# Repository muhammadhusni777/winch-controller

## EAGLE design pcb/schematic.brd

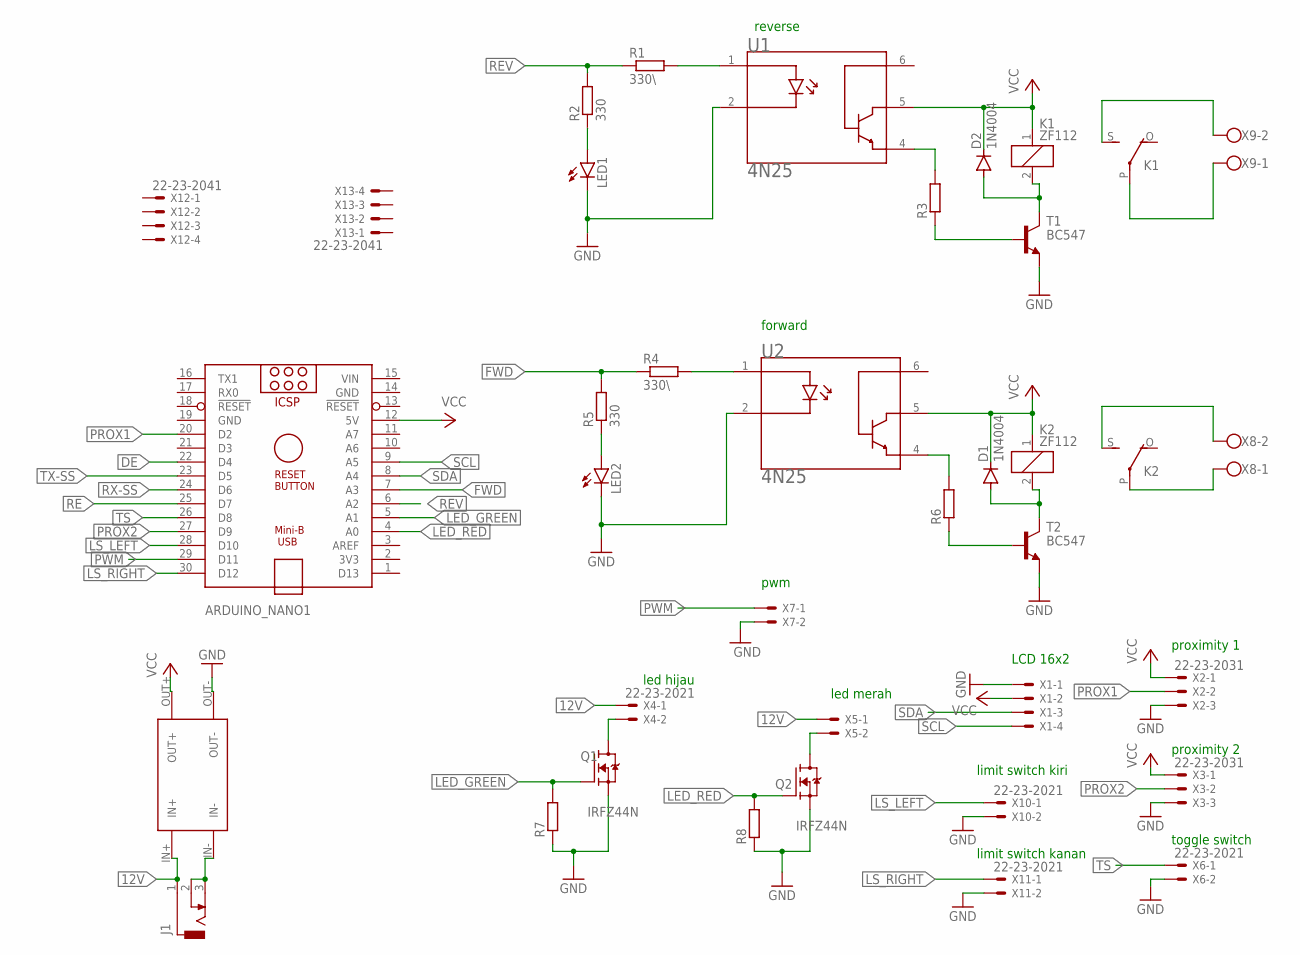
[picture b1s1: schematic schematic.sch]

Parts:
ARDUINO_NANO1: ARDUINO_NANO
D1, D2: 1N4004; DO41-10
J1: DCJ0303
K1, K2: ZF112
LED1, LED2: LED5MM
Q1, Q2: IRFZ44N; TO254P1016X419X2286-3
R1, R4: 330\; 0207/10
R2, R5: 330; 0207/10
R3, R6, R7, R8: R-EU_0207/10; 0207/10
T1, T2: BC547; TO92
U1, U2: 4N25; DIP762W50P254L712H400Q6N
U$1: XL4005
X1, X12, X13: 22-23-2041
X2, X3: 22-23-2031
X4, X5, X6, X7, X10, X11: 22-23-2021
X8, X9: W237-102

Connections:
12V: J1.1, U$1.IN+, X4.1, X5.1
DE: ARDUINO_NANO1.22 (D4)
FWD: ARDUINO_NANO1.7 (A3), R4.1, R5.2
GND: ARDUINO_NANO1.14 (GND), ARDUINO_NANO1.19 (GND), LED1.K (C), LED2.K (C), Q1.3 (S), Q2.3 (S), R7.1, R8.1, T1.1 (E), T2.1 (E), U1.2 (K), U2.2 (K), U$1.OUT-, X1.1, X2.3, X3.3, X6.2, X7.2, X10.2, X11.2
LED_GREEN: ARDUINO_NANO1.5 (A1), Q1.1 (G), R7.2
LED_RED: ARDUINO_NANO1.4 (A0), Q2.1 (G), R8.2
LS_LEFT: ARDUINO_NANO1.28 (D10), X10.1
LS_RIGHT: ARDUINO_NANO1.30 (D12), X11.1
unnamed: R1.2, U1.1 (A)
unnamed: LED1.A, R2.1
unnamed: R3.2, U1.4 (E)
unnamed: R3.1, T1.2 (B)
unnamed: D2.A, K1.2, T1.3 (C)
unnamed: R4.2, U2.1 (A)
unnamed: LED2.A, R5.1
unnamed: R6.2, U2.4 (E)
unnamed: R6.1, T2.2 (B)
unnamed: D1.A, K2.2, T2.3 (C)
unnamed: Q1.2 (D), X4.2
unnamed: Q2.2 (D), X5.2
unnamed: K1.P, X9.1
unnamed: K1.S, X9.2
unnamed: K2.S, X8.2
unnamed: K2.P, X8.1
unnamed: J1.2, J1.3, U$1.IN-
PROX1: ARDUINO_NANO1.20 (D2), X2.2
PROX2: ARDUINO_NANO1.27 (D9), X3.2
PWM: ARDUINO_NANO1.29 (D11), X7.1
RE: ARDUINO_NANO1.25 (D7)
REV: ARDUINO_NANO1.6 (A2), R1.1, R2.2
RX-SS: ARDUINO_NANO1.24 (D6)
SCL: ARDUINO_NANO1.9 (A5), X1.4
SDA: ARDUINO_NANO1.8 (A4), X1.3
TS: ARDUINO_NANO1.26 (D8), X6.1
TX-SS: ARDUINO_NANO1.23 (D5)
VCC: ARDUINO_NANO1.12 (5V), D1.C, D2.C, K1.1, K2.1, U1.5 (C), U2.5 (C), U$1.OUT+, X1.2, X2.1, X3.1
VIN: ARDUINO_NANO1.15 (VIN)

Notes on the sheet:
LCD 16x2
proximity 1
proximity 2
toggle switch
led merah
led hijau
forward
reverse
pwm
limit switch kiri
limit switch kanan

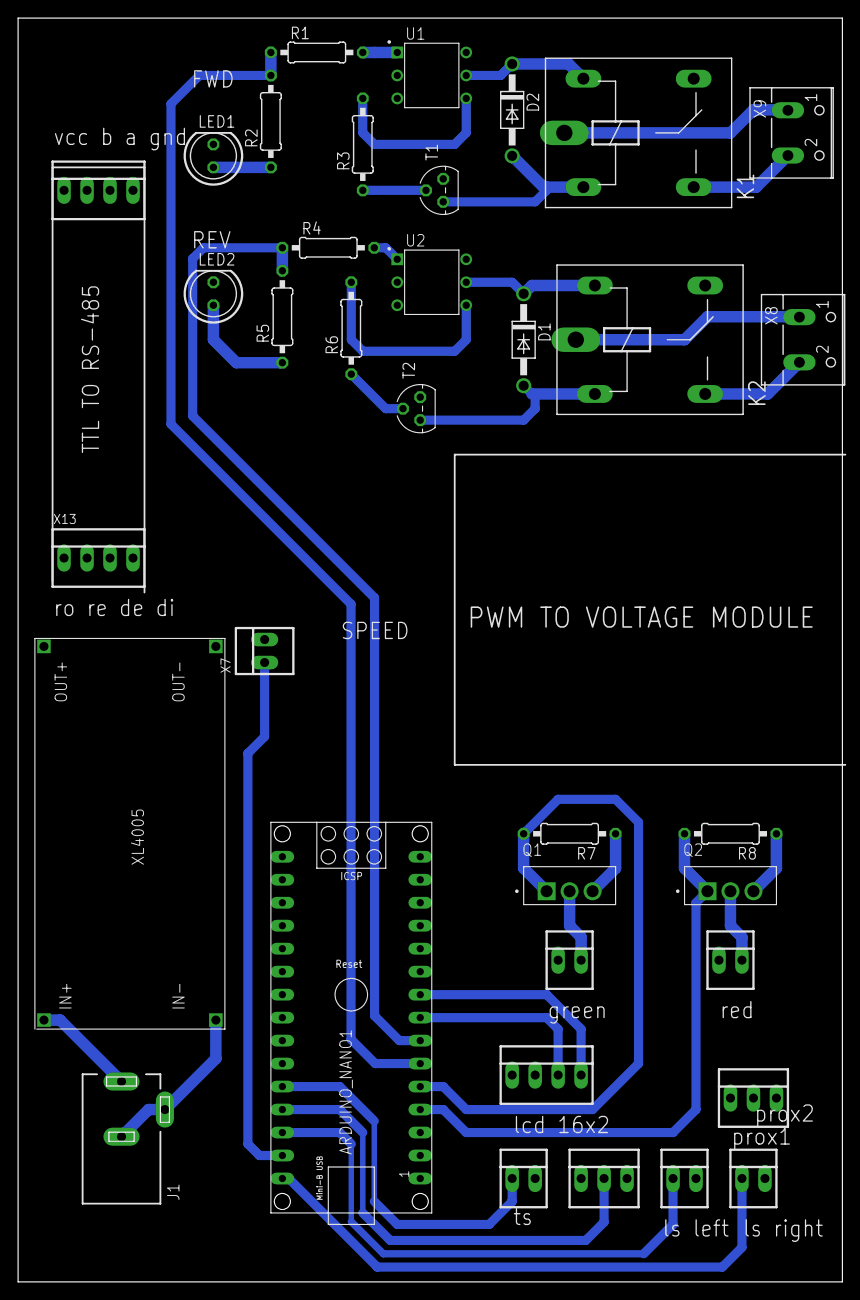
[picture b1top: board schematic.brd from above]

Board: 2 copper layers, 91.1 x 139.7 mm, 36 parts (0 on the bottom side), 32 nets.

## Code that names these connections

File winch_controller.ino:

#include <LiquidCrystal_I2C.h>
LiquidCrystal_I2C lcd(0x27, 16, 2); 

#define prox1 3 //ujung kanan
#define prox2 4 //ujung kiri

#define sw 10 // toggle switch
#define hijau 8 // lampu
#define fwd 9
#define off 7

#define CLK 9
#define DT 2

const int pwmPin = 11;  // Pin PWM pada Arduino Uno
const int rpmTarget = 1000;  // Kecepatan target dalam RPM

const int sensorPin = 2;  // Pin digital yang terhubung ke output sensor
volatile unsigned long count = 0;  // Variabel untuk menyimpan jumlah putaran
const float jarakAntarGigi = 2.0;  // Jarak antara setiap gigi dalam sentimeter

unsigned long pulse_per_second = 0;

unsigned long time_per_second;
unsigned long time_per_second_prev;

int currentStateCLK;
int lastStateCLK;
int p1;
int p2;
bool p1_lock;
bool p2_lock;

float counter = 0;

bool direction_motor;
bool initializing;

void setup() {

  lcd.init();
  lcd.backlight();
  pinMode(prox1,INPUT_PULLUP);
  pinMode(prox2,INPUT_PULLUP);
  pinMode(off,INPUT_PULLUP);

  pinMode(pwmPin, OUTPUT);
  analogWrite(pwmPin, 0);  // Inisialisasi PWM dengan duty cycle 0

  pinMode(sw,INPUT_PULLUP);
  pinMode(hijau,OUTPUT);
  pinMode(fwd,OUTPUT);

  pinMode(sensorPin, INPUT_PULLUP);
  attachInterrupt(0, updateEncoder, CHANGE);
  initializing = false;

}

void loop() {
    time_per_second = millis() - time_per_second_prev;
    
    if (time_per_second > 1000){
      pulse_per_second = counter;
      time_per_second_prev = millis();
      counter = 0;
    }
     
    if (digitalRead(sw) == HIGH) {
      digitalWrite(hijau, HIGH);
      int p1 = !digitalRead(prox1);
      int p2 = !digitalRead(prox2);

      if (initializing == false){
          if (counter  > 0){
              direction_motor = true;
          }
          else{
              direction_motor = false;
          }
          p1_lock = false;
          p2_lock = false;
      }

        
      if (p1 == HIGH && p1_lock == false){
          initializing = true;
          p1_lock = true;
          p2_lock = false;
          direction_motor = !direction_motor;   
      }
        
       if (p2 == HIGH && p2_lock == false){
           initializing = true;
           p1_lock = false;
           p2_lock = true;
           direction_motor = !direction_motor;
       }
       
       if (direction_motor == true){
        lcd.setCursor(0,1);
        lcd.print("forward");
       } else {
        lcd.setCursor(0,1);
        lcd.print("reverse");
       }


            
       }  





        
    else{
        digitalWrite(hijau, LOW);
        initializing = false;
        lcd.clear();
    }
    digitalWrite(fwd, direction_motor);
        
    

}


void updateEncoder(){
  
  currentStateCLK = digitalRead(CLK);
  if ((currentStateCLK != lastStateCLK)  && (currentStateCLK == 1)){
    if (digitalRead(DT) != currentStateCLK) {
      counter = counter - 1;
    } else {
      counter = counter + 1;
    }
  }
  
  lastStateCLK = currentStateCLK;
  
}
